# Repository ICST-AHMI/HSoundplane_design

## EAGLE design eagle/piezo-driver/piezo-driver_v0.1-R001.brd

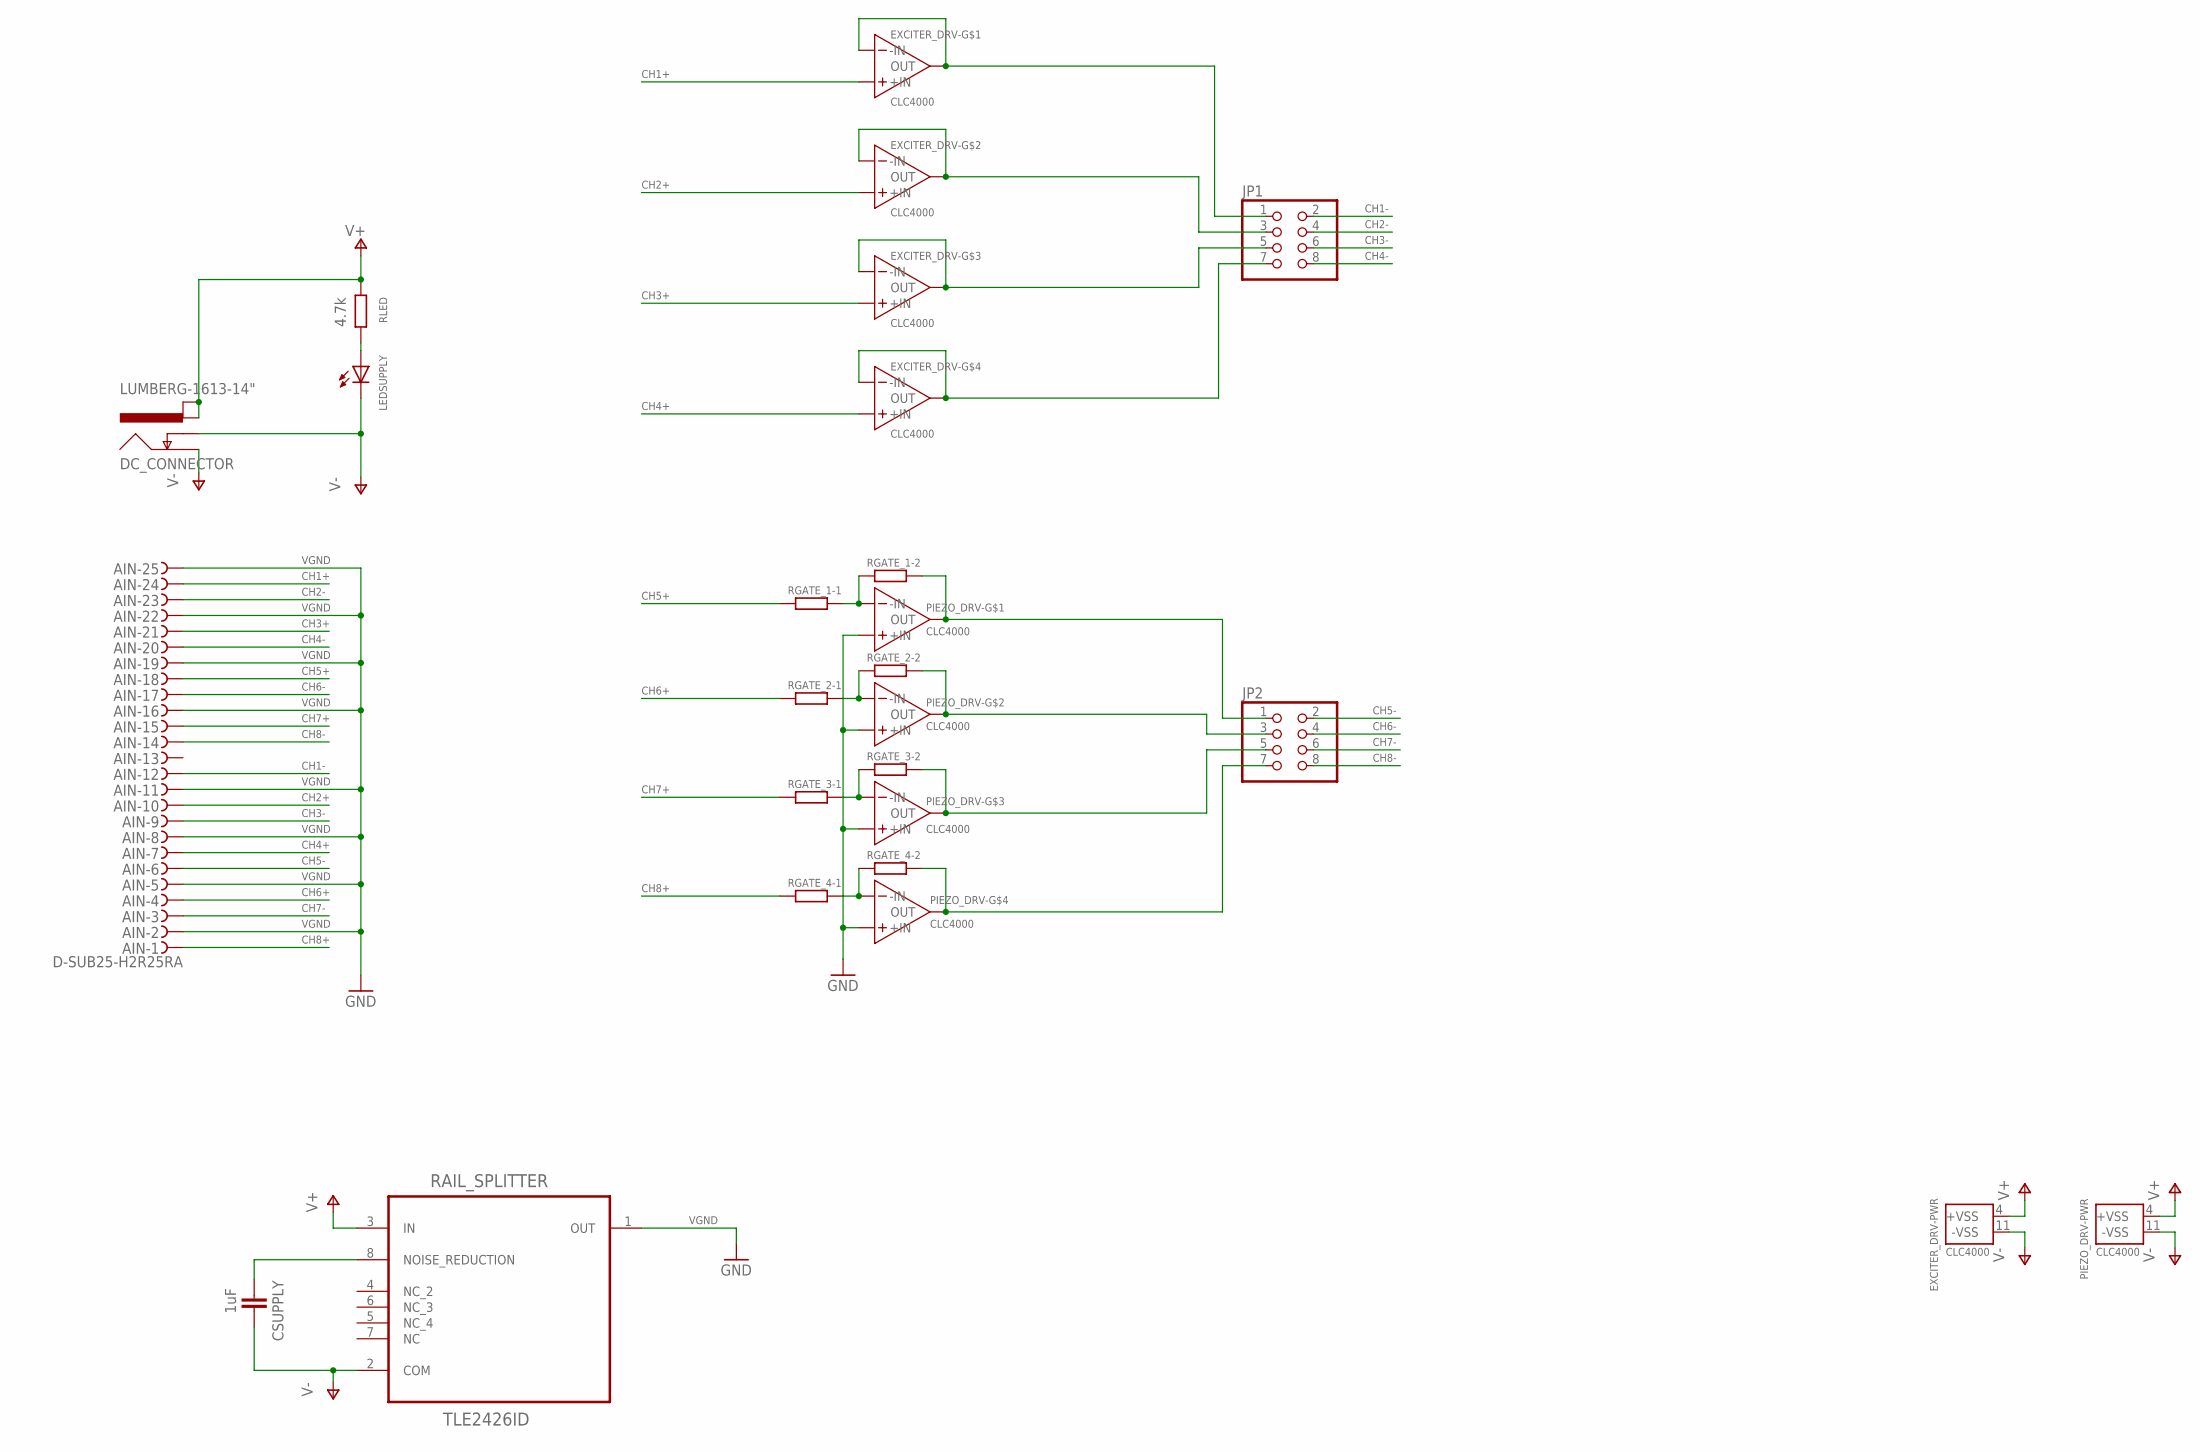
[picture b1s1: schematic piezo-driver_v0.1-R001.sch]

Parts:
AIN: D-SUB25-H2R25RA; H2R25RA
CSUPPLY: 1uF; C0603
DC_CONNECTOR: LUMBERG-1613-14"; LUMBERG-1613_14
EXCITER_DRV: CLC4000; SOIC-14
JP1, JP2: PINHD-2X4/90; 2X04/90
LEDSUPPLY: LED3MM
PIEZO_DRV: CLC4000; SOIC-14
RAIL_SPLITTER: TLE2426ID; SOIC127P600X175-8N
RGATE_1-1, RGATE_1-2, RGATE_2-1, RGATE_2-2, RGATE_3-1, RGATE_3-2, RGATE_4-1, RGATE_4-2: R-EU_R0805; R0805
RLED: 4.7k; R0805

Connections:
CH1+: AIN.24, EXCITER_DRV.3 (+IN)
CH1-: AIN.12, JP1.2
CH2+: AIN.10, EXCITER_DRV.5 (+IN)
CH2-: AIN.23, JP1.4
CH3+: AIN.21, EXCITER_DRV.10 (+IN)
CH3-: AIN.9, JP1.6
CH4+: AIN.7, EXCITER_DRV.12 (+IN)
CH4-: AIN.20, JP1.8
CH5+: AIN.18, RGATE_1-1.1
CH5-: AIN.6, JP2.2
CH6+: AIN.4, RGATE_2-1.1
CH6-: AIN.17, JP2.4
CH7+: AIN.15, RGATE_3-1.1
CH7-: AIN.3, JP2.6
CH8+: AIN.1, RGATE_4-1.1
CH8-: AIN.14, JP2.8
unnamed: EXCITER_DRV.1 (OUT), EXCITER_DRV.2 (-IN), JP1.1
unnamed: EXCITER_DRV.6 (-IN), EXCITER_DRV.7 (OUT), JP1.3
unnamed: EXCITER_DRV.8 (OUT), EXCITER_DRV.9 (-IN), JP1.5
unnamed: EXCITER_DRV.13 (-IN), EXCITER_DRV.14 (OUT), JP1.7
unnamed: CSUPPLY.1, RAIL_SPLITTER.8 (NOISE_REDUCTION)
unnamed: PIEZO_DRV.2 (-IN), RGATE_1-1.2, RGATE_1-2.1
unnamed: JP2.1, PIEZO_DRV.1 (OUT), RGATE_1-2.2
unnamed: PIEZO_DRV.6 (-IN), RGATE_2-1.2, RGATE_2-2.1
unnamed: JP2.3, PIEZO_DRV.7 (OUT), RGATE_2-2.2
unnamed: PIEZO_DRV.9 (-IN), RGATE_3-1.2, RGATE_3-2.1
unnamed: JP2.5, PIEZO_DRV.8 (OUT), RGATE_3-2.2
unnamed: PIEZO_DRV.13 (-IN), RGATE_4-1.2, RGATE_4-2.1
unnamed: JP2.7, PIEZO_DRV.14 (OUT), RGATE_4-2.2
unnamed: LEDSUPPLY.A, RLED.1
V+: DC_CONNECTOR.3 (PWR_1), DC_CONNECTOR.4 (PWR_2), EXCITER_DRV.4 (+VSS), PIEZO_DRV.4 (+VSS), RAIL_SPLITTER.3 (IN), RLED.2
V-: CSUPPLY.2, DC_CONNECTOR.1 (GND), DC_CONNECTOR.2 (GND_INS), EXCITER_DRV.11 (-VSS), LEDSUPPLY.K (C), PIEZO_DRV.11 (-VSS), RAIL_SPLITTER.2 (COM)
VGND: AIN.2, AIN.5, AIN.8, AIN.11, AIN.16, AIN.19, AIN.22, AIN.25, PIEZO_DRV.3 (+IN), PIEZO_DRV.5 (+IN), PIEZO_DRV.10 (+IN), PIEZO_DRV.12 (+IN), RAIL_SPLITTER.1 (OUT)

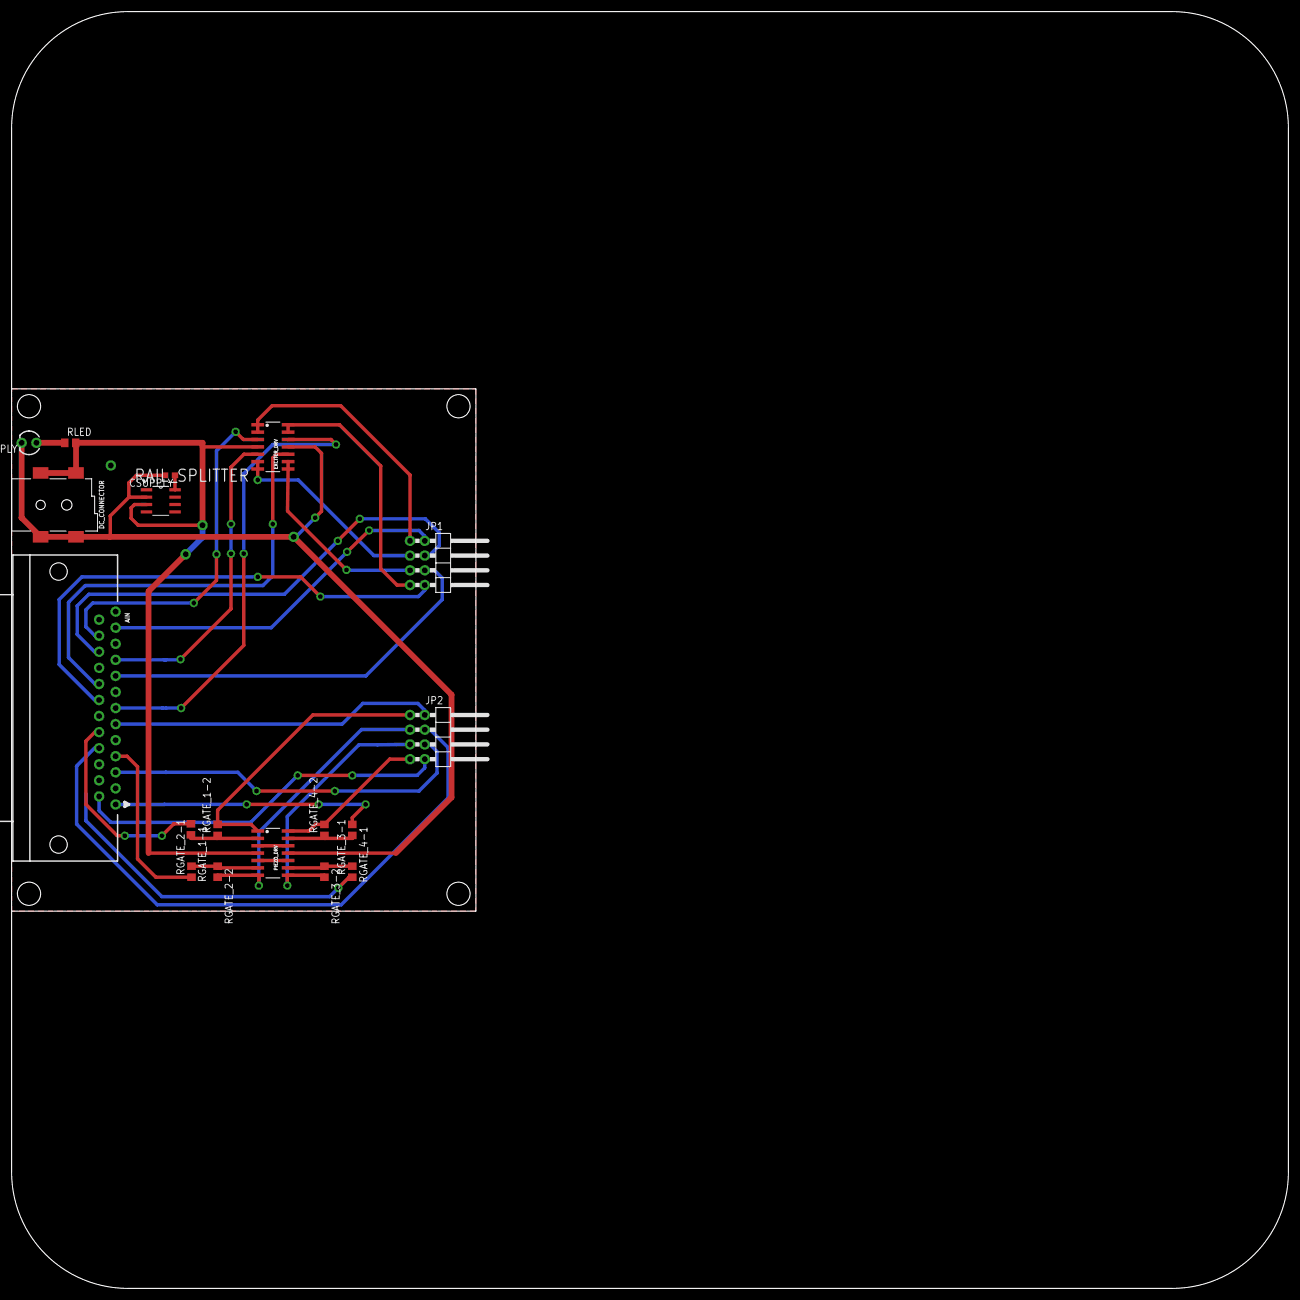
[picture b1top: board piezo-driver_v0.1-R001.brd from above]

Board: 2 copper layers, 220.0 x 220.0 mm, 18 parts (0 on the bottom side), 33 nets.

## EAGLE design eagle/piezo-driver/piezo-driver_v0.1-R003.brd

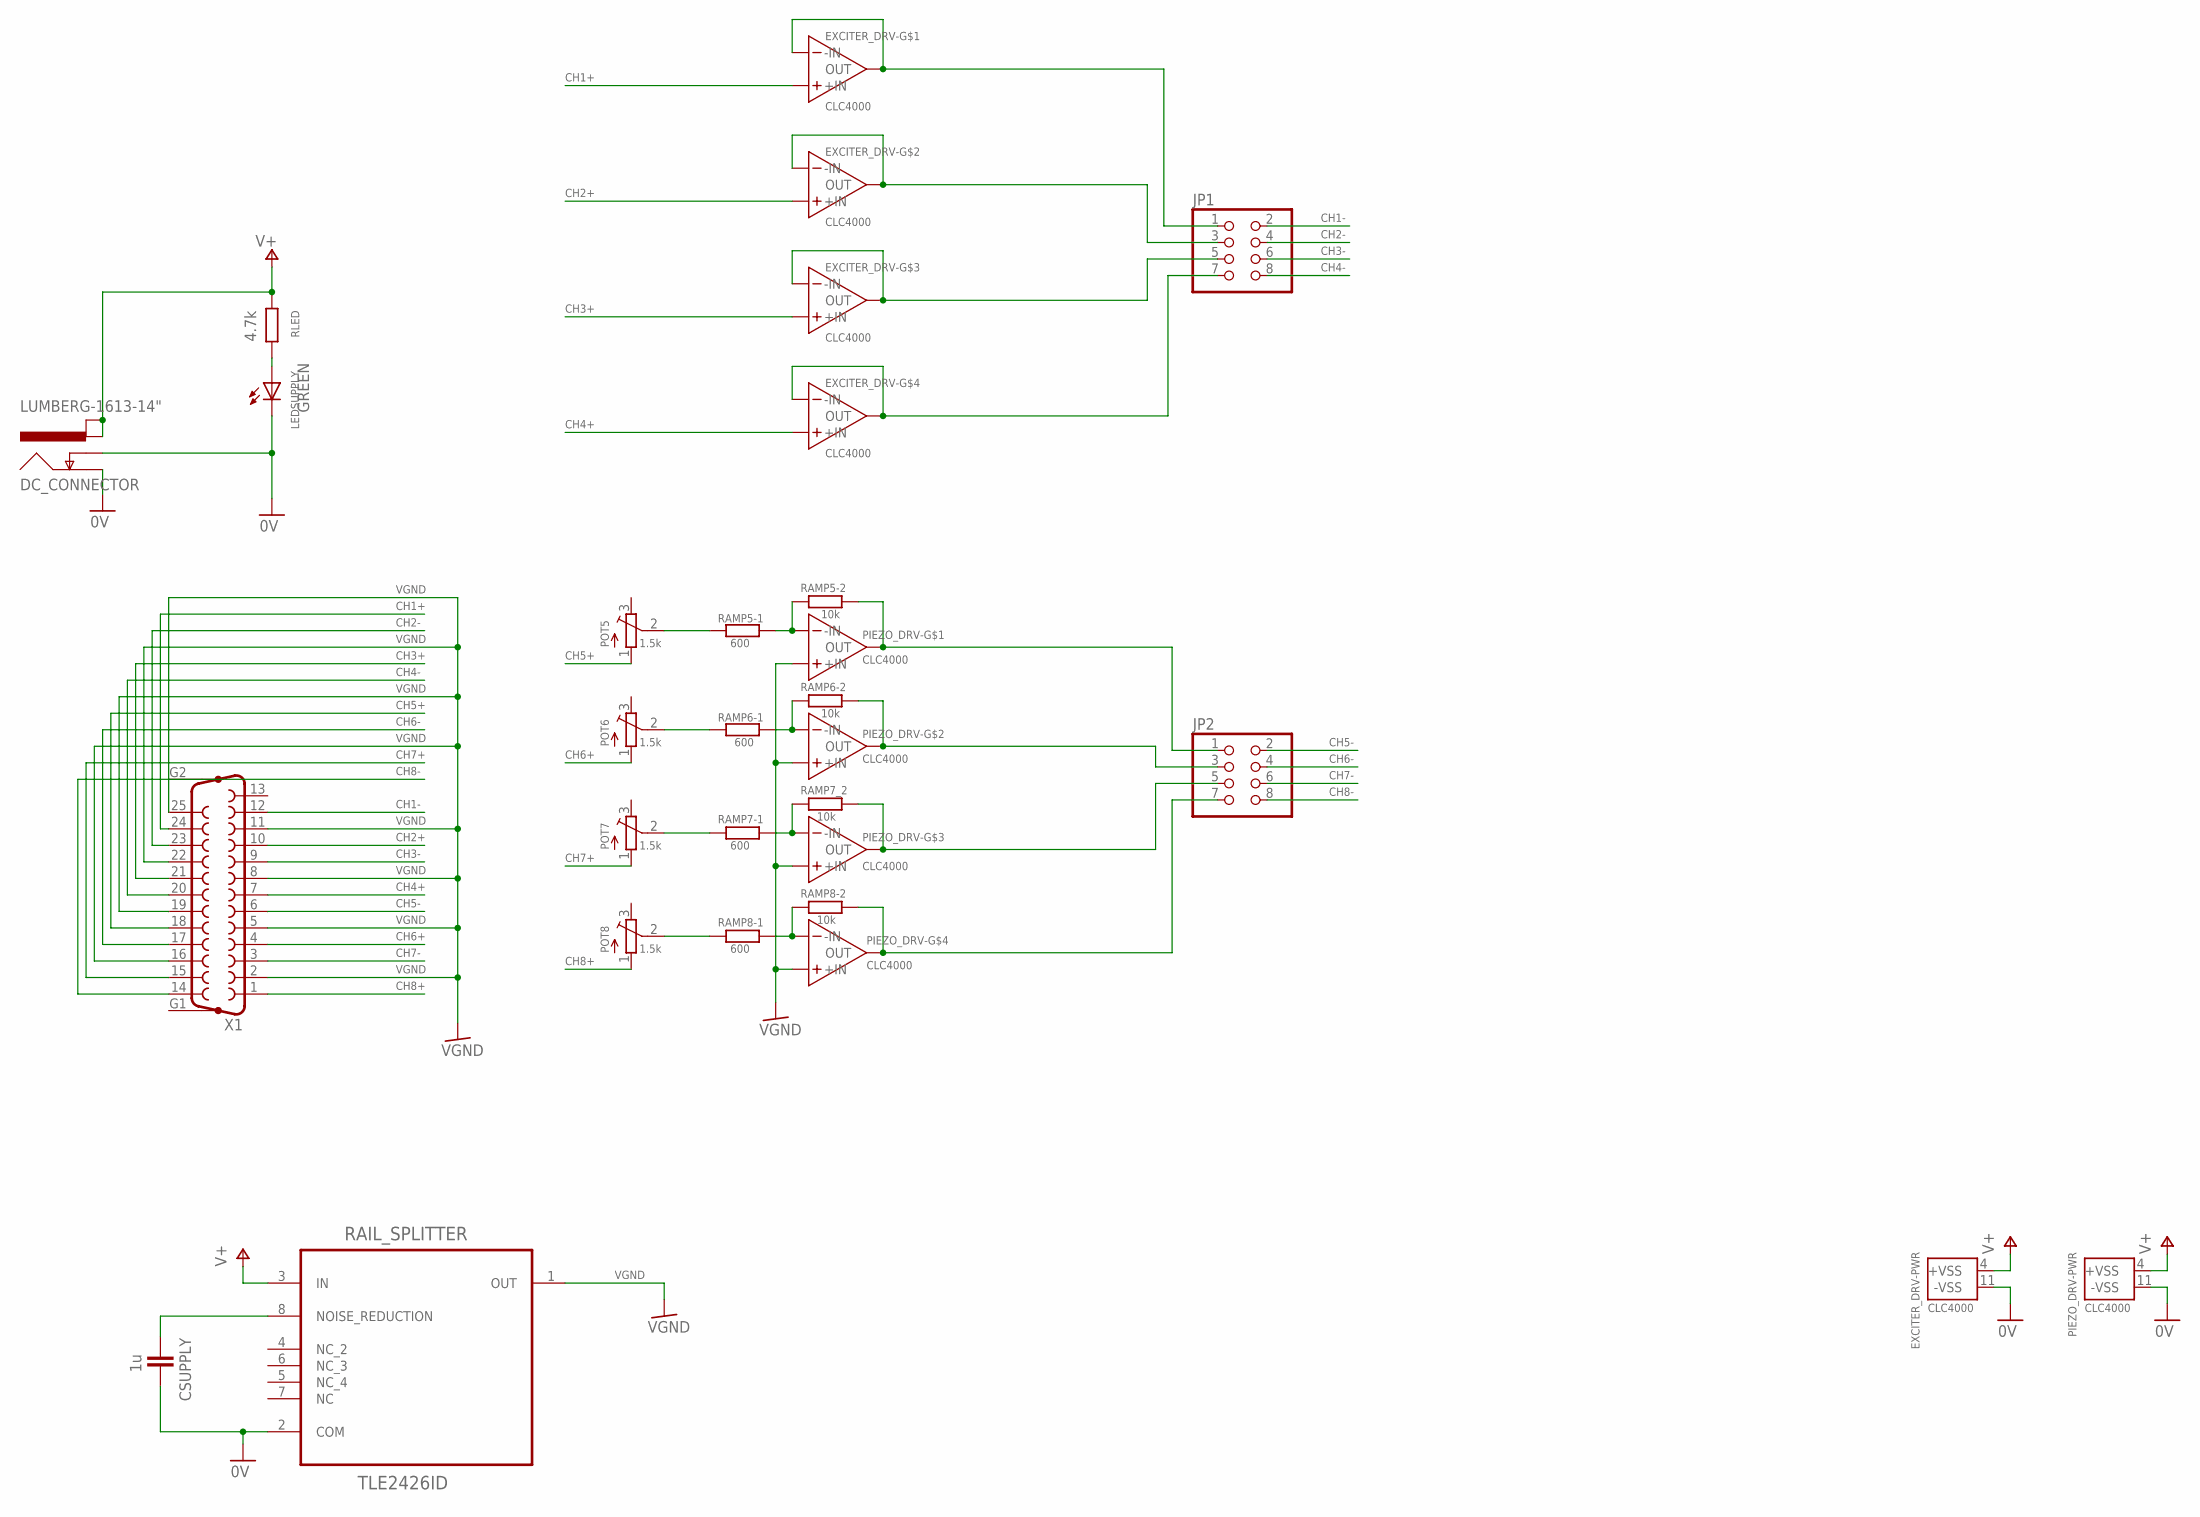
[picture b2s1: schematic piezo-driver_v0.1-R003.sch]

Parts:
CSUPPLY: 1u; C0603
DC_CONNECTOR: LUMBERG-1613-14"; LUMBERG-1613_14
EXCITER_DRV: CLC4000; SOIC-14
JP1, JP2: PINHD-2X4/90; 2X04/90
LEDSUPPLY: GREEN; LED3MM
PIEZO_DRV: CLC4000; SOIC-14
POT5, POT6, POT7, POT8: 1.5k; PVG3
RAIL_SPLITTER: TLE2426ID; SOIC127P600X175-8N
RAMP5-1, RAMP6-1, RAMP7-1, RAMP8-1: 600; R0805
RAMP5-2, RAMP6-2, RAMP7_2, RAMP8-2: 10k; R0805
RLED: 4.7k; R0805
X1: F25HP

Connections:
CH1+: EXCITER_DRV.3 (+IN), X1.24
CH1-: JP1.2, X1.12
CH2+: EXCITER_DRV.5 (+IN), X1.10
CH2-: JP1.4, X1.23
CH3+: EXCITER_DRV.10 (+IN), X1.21
CH3-: JP1.6, X1.9
CH4+: EXCITER_DRV.12 (+IN), X1.7
CH4-: JP1.8, X1.20
CH5+: POT5.1 (A), X1.18
CH5-: JP2.2, X1.6
CH6+: POT6.1 (A), X1.4
CH6-: JP2.4, X1.17
CH7+: POT7.1 (A), X1.15
CH7-: JP2.6, X1.3
CH8+: POT8.1 (A), X1.1
CH8-: JP2.8, X1.14
unnamed: EXCITER_DRV.1 (OUT), EXCITER_DRV.2 (-IN), JP1.1
unnamed: EXCITER_DRV.6 (-IN), EXCITER_DRV.7 (OUT), JP1.3
unnamed: EXCITER_DRV.8 (OUT), EXCITER_DRV.9 (-IN), JP1.5
unnamed: EXCITER_DRV.13 (-IN), EXCITER_DRV.14 (OUT), JP1.7
unnamed: CSUPPLY.1, RAIL_SPLITTER.8 (NOISE_REDUCTION)
unnamed: PIEZO_DRV.2 (-IN), RAMP5-1.2, RAMP5-2.1
unnamed: JP2.1, PIEZO_DRV.1 (OUT), RAMP5-2.2
unnamed: PIEZO_DRV.6 (-IN), RAMP6-1.2, RAMP6-2.1
unnamed: JP2.3, PIEZO_DRV.7 (OUT), RAMP6-2.2
unnamed: PIEZO_DRV.9 (-IN), RAMP7-1.2, RAMP7_2.1
unnamed: JP2.5, PIEZO_DRV.8 (OUT), RAMP7_2.2
unnamed: PIEZO_DRV.13 (-IN), RAMP8-1.2, RAMP8-2.1
unnamed: JP2.7, PIEZO_DRV.14 (OUT), RAMP8-2.2
unnamed: LEDSUPPLY.A, RLED.1
unnamed: POT5.2 (S), RAMP5-1.1
unnamed: POT6.2 (S), RAMP6-1.1
unnamed: POT7.2 (S), RAMP7-1.1
unnamed: POT8.2 (S), RAMP8-1.1
V+: DC_CONNECTOR.3 (PWR_1), DC_CONNECTOR.4 (PWR_2), EXCITER_DRV.4 (+VSS), PIEZO_DRV.4 (+VSS), RAIL_SPLITTER.3 (IN), RLED.2
V-: CSUPPLY.2, DC_CONNECTOR.1 (GND), DC_CONNECTOR.2 (GND_INS), EXCITER_DRV.11 (-VSS), LEDSUPPLY.K (C), PIEZO_DRV.11 (-VSS), RAIL_SPLITTER.2 (COM)
VGND: PIEZO_DRV.3 (+IN), PIEZO_DRV.5 (+IN), PIEZO_DRV.10 (+IN), PIEZO_DRV.12 (+IN), RAIL_SPLITTER.1 (OUT), X1.2, X1.5, X1.8, X1.11, X1.16, X1.19, X1.22, X1.25

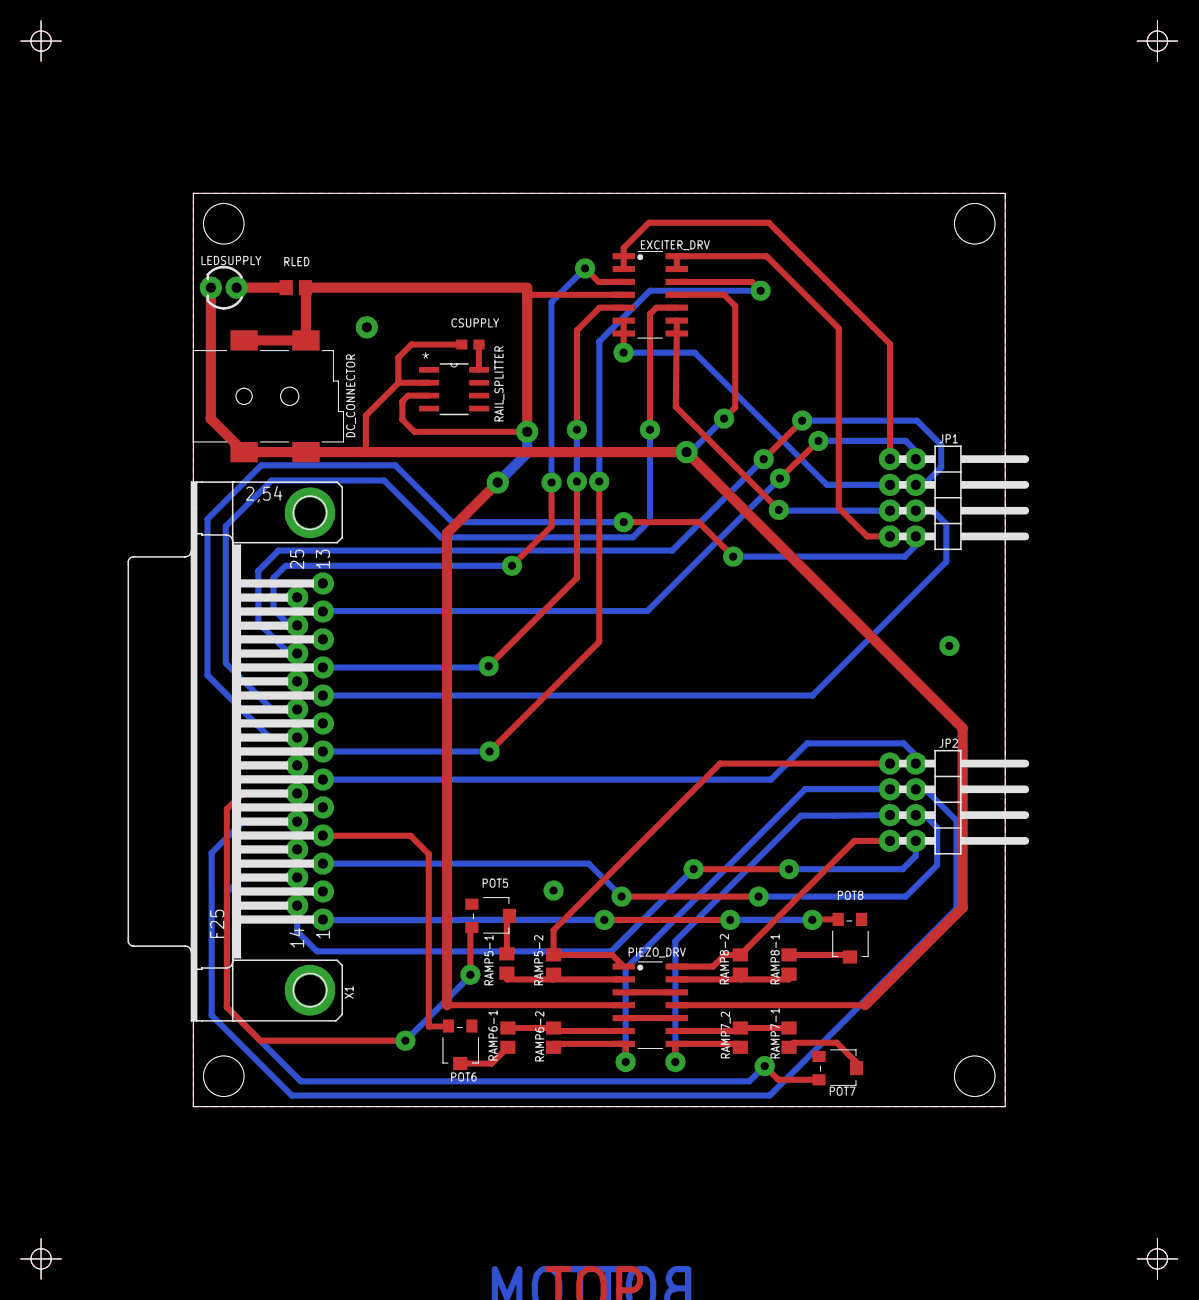
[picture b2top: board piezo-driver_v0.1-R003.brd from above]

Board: 2 copper layers, 80.0 x 90.0 mm, 22 parts (0 on the bottom side), 37 nets.

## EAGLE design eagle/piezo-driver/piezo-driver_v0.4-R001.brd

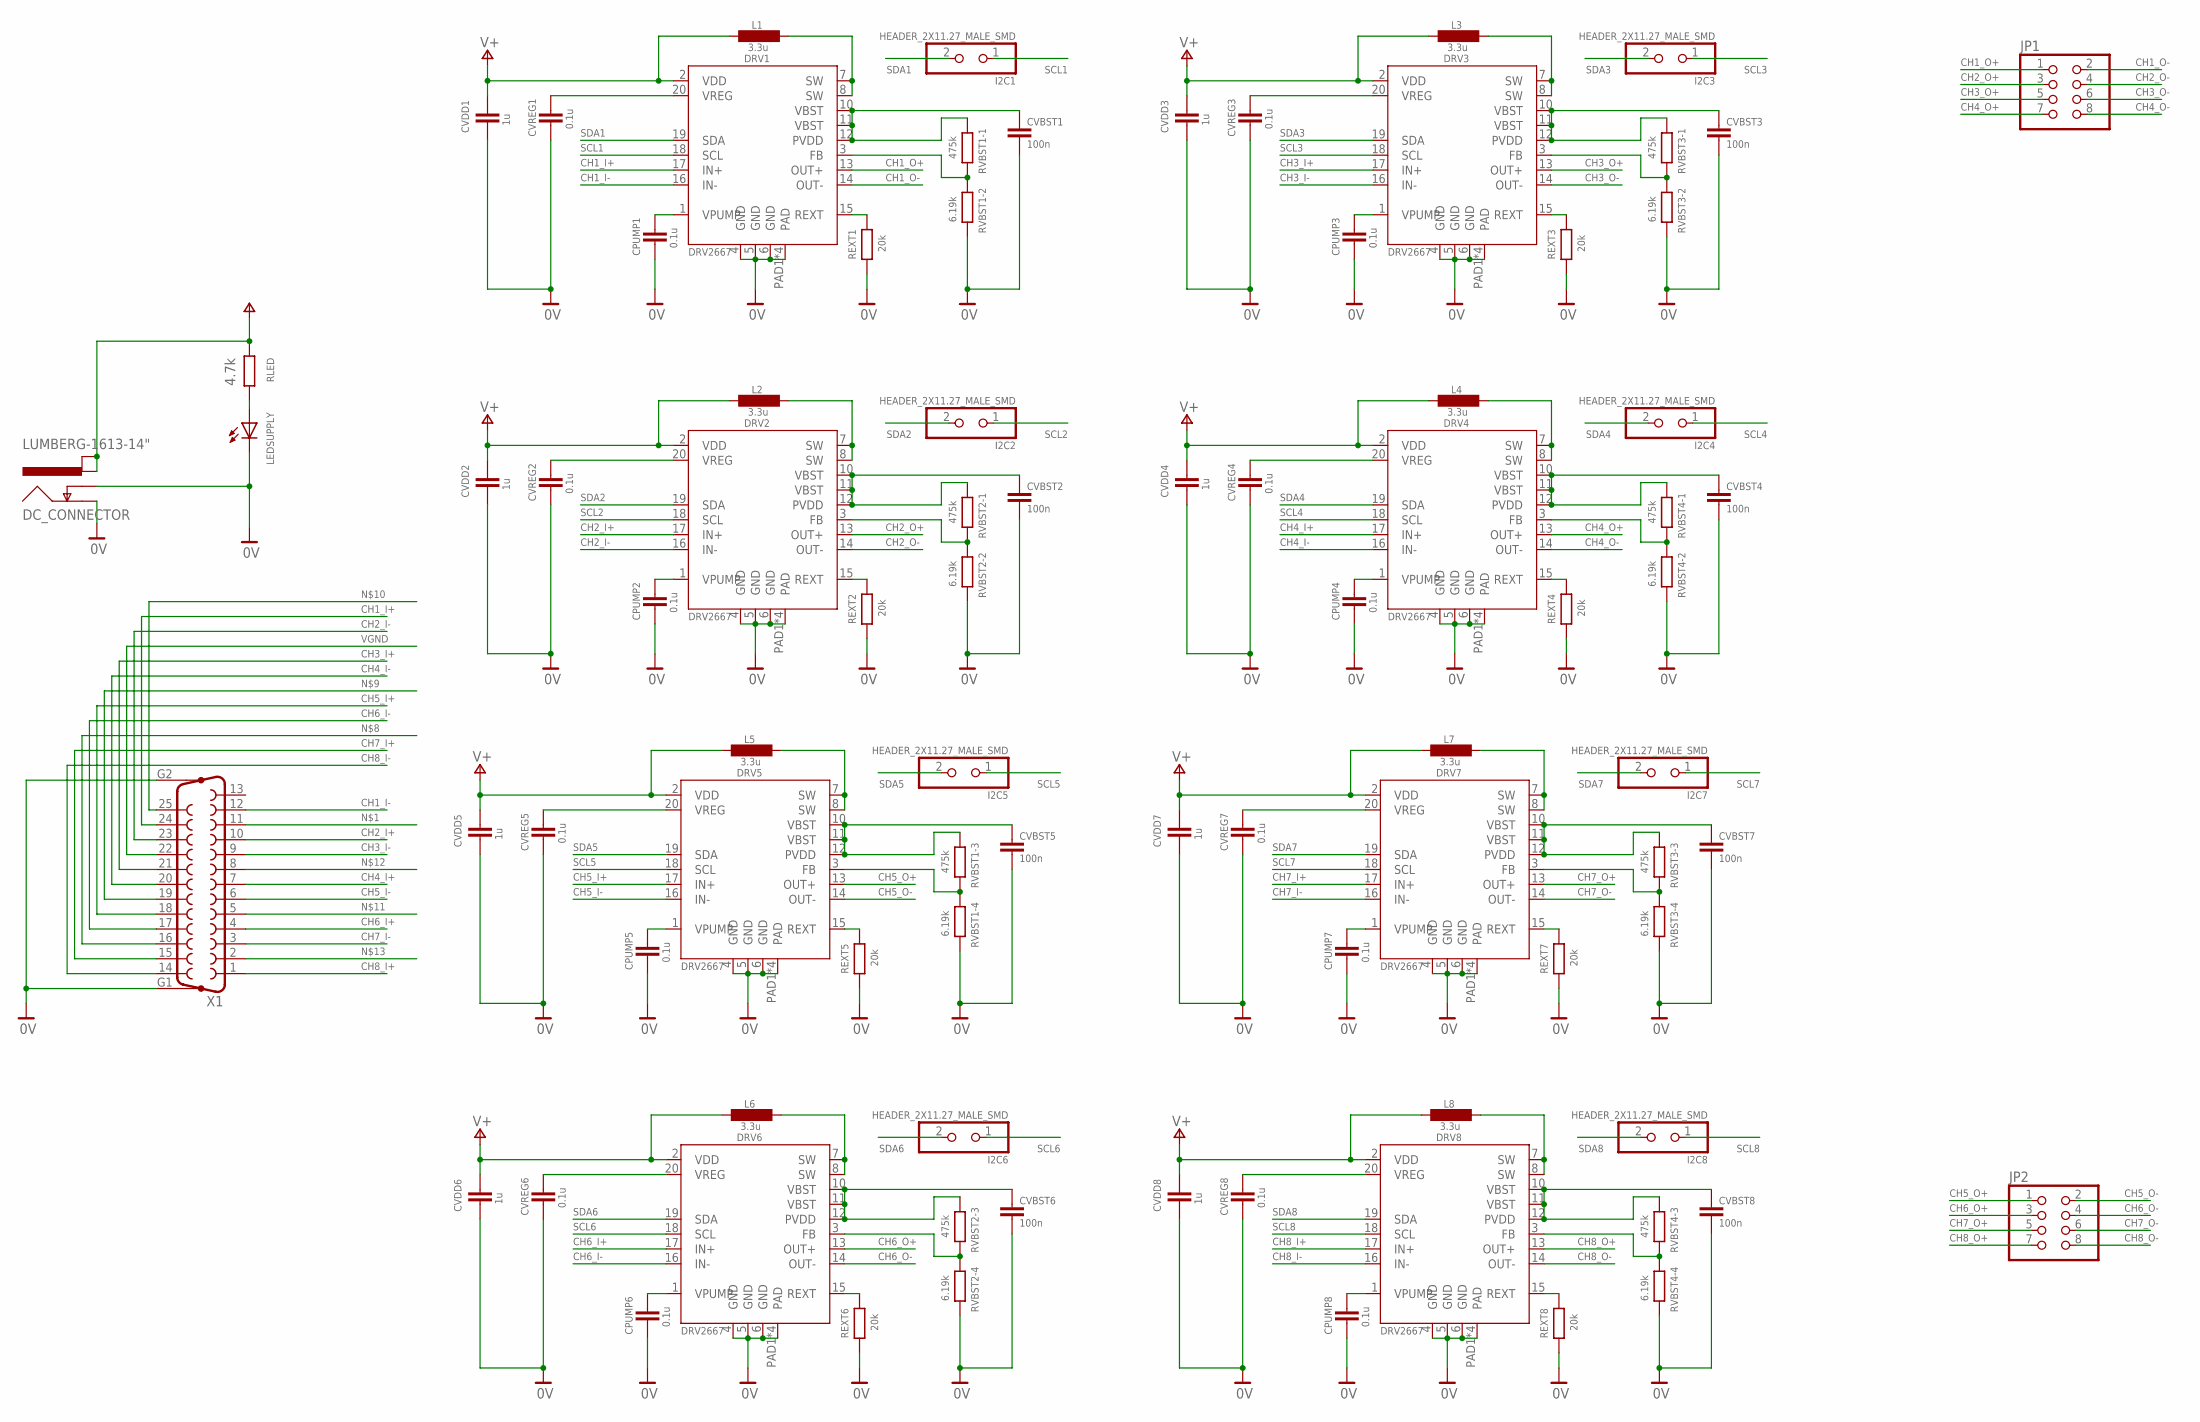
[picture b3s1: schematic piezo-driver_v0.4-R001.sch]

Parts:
CPUMP1, CPUMP2, CPUMP3, CPUMP4, CPUMP5, CPUMP6, CPUMP7, CPUMP8: 0.1u; C0805
CVBST1, CVBST2, CVBST3, CVBST4, CVBST5, CVBST6, CVBST7, CVBST8: 100n; C0805
CVDD1, CVDD2, CVDD3, CVDD4, CVDD5, CVDD6, CVDD7, CVDD8: 1u; C0805
CVREG1, CVREG2, CVREG3, CVREG4, CVREG5, CVREG6, CVREG7, CVREG8: 0.1u; C0805
DC_CONNECTOR: LUMBERG-1613-14"; LUMBERG-1613_14
DRV1, DRV2, DRV3, DRV4, DRV5, DRV6, DRV7, DRV8: DRV2667QFN; QFN400X400
I2C1, I2C2, I2C3, I2C4, I2C5, I2C6, I2C7, I2C8: HEADER_2X11.27_MALE_SMD; 2X01_1.27_SMD
JP1, JP2: PINHD-2X4/90; 2X04/90
L1, L2, L3, L4, L5, L6, L7, L8: 3.3u; L3225M
LEDSUPPLY: LED0603; LED-0603
REXT1, REXT2, REXT3, REXT4, REXT5, REXT6, REXT7, REXT8: 20k; R0805
RLED: 4.7k; R0805
RVBST1-1, RVBST1-3, RVBST2-1, RVBST2-3, RVBST3-1, RVBST3-3, RVBST4-1, RVBST4-3: 475k; R0805
RVBST1-2, RVBST1-4, RVBST2-2, RVBST2-4, RVBST3-2, RVBST3-4, RVBST4-2, RVBST4-4: 6.19k; R0805
X1: F25HP

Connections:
0V: CPUMP1.2, CPUMP2.2, CPUMP3.2, CPUMP4.2, CPUMP5.2, CPUMP6.2, CPUMP7.2, CPUMP8.2, CVBST1.2, CVBST2.2, CVBST3.2, CVBST4.2, CVBST5.2, CVBST6.2, CVBST7.2, CVBST8.2, CVDD1.2, CVDD2.2, CVDD3.2, CVDD4.2, CVDD5.2, CVDD6.2, CVDD7.2, CVDD8.2, CVREG1.2, CVREG2.2, CVREG3.2, CVREG4.2, CVREG5.2, CVREG6.2, CVREG7.2, CVREG8.2, DC_CONNECTOR.1 (GND), DC_CONNECTOR.2 (GND_INS), DRV1.4 (GND), DRV1.5 (GND), DRV1.6 (GND), DRV1.PAD1 (PAD), DRV1.PAD2 (PAD), DRV1.PAD3 (PAD), DRV1.PAD4 (PAD), DRV2.4 (GND), DRV2.5 (GND), DRV2.6 (GND), DRV2.PAD1 (PAD), DRV2.PAD2 (PAD), DRV2.PAD3 (PAD), DRV2.PAD4 (PAD), DRV3.4 (GND), DRV3.5 (GND), DRV3.6 (GND), DRV3.PAD1 (PAD), DRV3.PAD2 (PAD), DRV3.PAD3 (PAD), DRV3.PAD4 (PAD), DRV4.4 (GND), DRV4.5 (GND), DRV4.6 (GND), DRV4.PAD1 (PAD), DRV4.PAD2 (PAD), DRV4.PAD3 (PAD), DRV4.PAD4 (PAD), DRV5.4 (GND), DRV5.5 (GND), DRV5.6 (GND), DRV5.PAD1 (PAD), DRV5.PAD2 (PAD), DRV5.PAD3 (PAD), DRV5.PAD4 (PAD), DRV6.4 (GND), DRV6.5 (GND), DRV6.6 (GND), DRV6.PAD1 (PAD), DRV6.PAD2 (PAD), DRV6.PAD3 (PAD), DRV6.PAD4 (PAD), DRV7.4 (GND), DRV7.5 (GND), DRV7.6 (GND), DRV7.PAD1 (PAD), DRV7.PAD2 (PAD), DRV7.PAD3 (PAD), DRV7.PAD4 (PAD), DRV8.4 (GND), DRV8.5 (GND), DRV8.6 (GND), DRV8.PAD1 (PAD), DRV8.PAD2 (PAD), DRV8.PAD3 (PAD), DRV8.PAD4 (PAD), LEDSUPPLY.C, REXT1.1, REXT2.1, REXT3.1, REXT4.1, REXT5.1, REXT6.1, REXT7.1, REXT8.1, RVBST1-2.1, RVBST1-4.1, RVBST2-2.1, RVBST2-4.1, RVBST3-2.1, RVBST3-4.1, RVBST4-2.1, RVBST4-4.1, X1.G1, X1.G2
CH1_I+: DRV1.17 (IN+), X1.24
CH1_I-: DRV1.16 (IN-), X1.12
CH1_O+: DRV1.13 (OUT+), JP1.1
CH1_O-: DRV1.14 (OUT-), JP1.2
CH2_I+: DRV2.17 (IN+), X1.10
CH2_I-: DRV2.16 (IN-), X1.23
CH2_O+: DRV2.13 (OUT+), JP1.3
CH2_O-: DRV2.14 (OUT-), JP1.4
CH3_I+: DRV3.17 (IN+), X1.21
CH3_I-: DRV3.16 (IN-), X1.9
CH3_O+: DRV3.13 (OUT+), JP1.5
CH3_O-: DRV3.14 (OUT-), JP1.6
CH4_I+: DRV4.17 (IN+), X1.7
CH4_I-: DRV4.16 (IN-), X1.20
CH4_O+: DRV4.13 (OUT+), JP1.7
CH4_O-: DRV4.14 (OUT-), JP1.8
CH5_I+: DRV5.17 (IN+), X1.18
CH5_I-: DRV5.16 (IN-), X1.6
CH5_O+: DRV5.13 (OUT+), JP2.1
CH5_O-: DRV5.14 (OUT-), JP2.2
CH6_I+: DRV6.17 (IN+), X1.4
CH6_I-: DRV6.16 (IN-), X1.17
CH6_O+: DRV6.13 (OUT+), JP2.3
CH6_O-: DRV6.14 (OUT-), JP2.4
CH7_I+: DRV7.17 (IN+), X1.15
CH7_I-: DRV7.16 (IN-), X1.3
CH7_O+: DRV7.13 (OUT+), JP2.5
CH7_O-: DRV7.14 (OUT-), JP2.6
CH8_I+: DRV8.17 (IN+), X1.1
CH8_I-: DRV8.16 (IN-), X1.14
CH8_O+: DRV8.13 (OUT+), JP2.7
CH8_O-: DRV8.14 (OUT-), JP2.8
unnamed: DRV1.7 (SW), DRV1.8 (SW), L1.1
unnamed: CVBST1.1, DRV1.10 (VBST), DRV1.11 (VBST), DRV1.12 (PVDD), RVBST1-1.2
unnamed: DRV1.3 (FB), RVBST1-1.1, RVBST1-2.2
unnamed: DRV1.15 (REXT), REXT1.2
unnamed: CPUMP1.1, DRV1.1 (VPUMP)
unnamed: CVREG1.1, DRV1.20 (VREG)
unnamed: DRV2.7 (SW), DRV2.8 (SW), L2.1
unnamed: LEDSUPPLY.A, RLED.1
unnamed: CVBST2.1, DRV2.10 (VBST), DRV2.11 (VBST), DRV2.12 (PVDD), RVBST2-1.2
unnamed: DRV2.3 (FB), RVBST2-1.1, RVBST2-2.2
unnamed: DRV2.15 (REXT), REXT2.2
unnamed: CPUMP2.1, DRV2.1 (VPUMP)
unnamed: CVREG2.1, DRV2.20 (VREG)
unnamed: DRV3.7 (SW), DRV3.8 (SW), L3.1
unnamed: CVBST3.1, DRV3.10 (VBST), DRV3.11 (VBST), DRV3.12 (PVDD), RVBST3-1.2
unnamed: DRV3.3 (FB), RVBST3-1.1, RVBST3-2.2
unnamed: DRV3.15 (REXT), REXT3.2
unnamed: CPUMP3.1, DRV3.1 (VPUMP)
unnamed: CVREG3.1, DRV3.20 (VREG)
unnamed: DRV4.7 (SW), DRV4.8 (SW), L4.1
unnamed: CVBST4.1, DRV4.10 (VBST), DRV4.11 (VBST), DRV4.12 (PVDD), RVBST4-1.2
unnamed: DRV4.3 (FB), RVBST4-1.1, RVBST4-2.2
unnamed: DRV4.15 (REXT), REXT4.2
unnamed: CPUMP4.1, DRV4.1 (VPUMP)
unnamed: CVREG4.1, DRV4.20 (VREG)
unnamed: DRV5.7 (SW), DRV5.8 (SW), L5.1
unnamed: CVBST5.1, DRV5.10 (VBST), DRV5.11 (VBST), DRV5.12 (PVDD), RVBST1-3.2
unnamed: DRV5.3 (FB), RVBST1-3.1, RVBST1-4.2
unnamed: DRV5.15 (REXT), REXT5.2
unnamed: CPUMP5.1, DRV5.1 (VPUMP)
unnamed: CVREG5.1, DRV5.20 (VREG)
unnamed: DRV6.7 (SW), DRV6.8 (SW), L6.1
unnamed: CVBST6.1, DRV6.10 (VBST), DRV6.11 (VBST), DRV6.12 (PVDD), RVBST2-3.2
unnamed: DRV6.3 (FB), RVBST2-3.1, RVBST2-4.2
unnamed: DRV6.15 (REXT), REXT6.2
unnamed: CPUMP6.1, DRV6.1 (VPUMP)
unnamed: CVREG6.1, DRV6.20 (VREG)
unnamed: DRV7.7 (SW), DRV7.8 (SW), L7.1
unnamed: CVBST7.1, DRV7.10 (VBST), DRV7.11 (VBST), DRV7.12 (PVDD), RVBST3-3.2
unnamed: DRV7.3 (FB), RVBST3-3.1, RVBST3-4.2
unnamed: DRV7.15 (REXT), REXT7.2
unnamed: CPUMP7.1, DRV7.1 (VPUMP)
unnamed: CVREG7.1, DRV7.20 (VREG)
unnamed: DRV8.7 (SW), DRV8.8 (SW), L8.1
unnamed: CVBST8.1, DRV8.10 (VBST), DRV8.11 (VBST), DRV8.12 (PVDD), RVBST4-3.2
unnamed: DRV8.3 (FB), RVBST4-3.1, RVBST4-4.2
unnamed: DRV8.15 (REXT), REXT8.2
unnamed: CPUMP8.1, DRV8.1 (VPUMP)
unnamed: CVREG8.1, DRV8.20 (VREG)
SCL1: DRV1.18 (SCL), I2C1.1
SCL2: DRV2.18 (SCL), I2C2.1
SCL3: DRV3.18 (SCL), I2C3.1
SCL4: DRV4.18 (SCL), I2C4.1
SCL5: DRV5.18 (SCL), I2C5.1
SCL6: DRV6.18 (SCL), I2C6.1
SCL7: DRV7.18 (SCL), I2C7.1
SCL8: DRV8.18 (SCL), I2C8.1
SDA1: DRV1.19 (SDA), I2C1.2
SDA2: DRV2.19 (SDA), I2C2.2
SDA3: DRV3.19 (SDA), I2C3.2
SDA4: DRV4.19 (SDA), I2C4.2
SDA5: DRV5.19 (SDA), I2C5.2
SDA6: DRV6.19 (SDA), I2C6.2
SDA7: DRV7.19 (SDA), I2C7.2
SDA8: DRV8.19 (SDA), I2C8.2
V+: CVDD1.1, CVDD2.1, CVDD3.1, CVDD4.1, CVDD5.1, CVDD6.1, CVDD7.1, CVDD8.1, DC_CONNECTOR.3 (PWR_1), DC_CONNECTOR.4 (PWR_2), DRV1.2 (VDD), DRV2.2 (VDD), DRV3.2 (VDD), DRV4.2 (VDD), DRV5.2 (VDD), DRV6.2 (VDD), DRV7.2 (VDD), DRV8.2 (VDD), L1.2, L2.2, L3.2, L4.2, L5.2, L6.2, L7.2, L8.2, RLED.2
VGND: X1.22

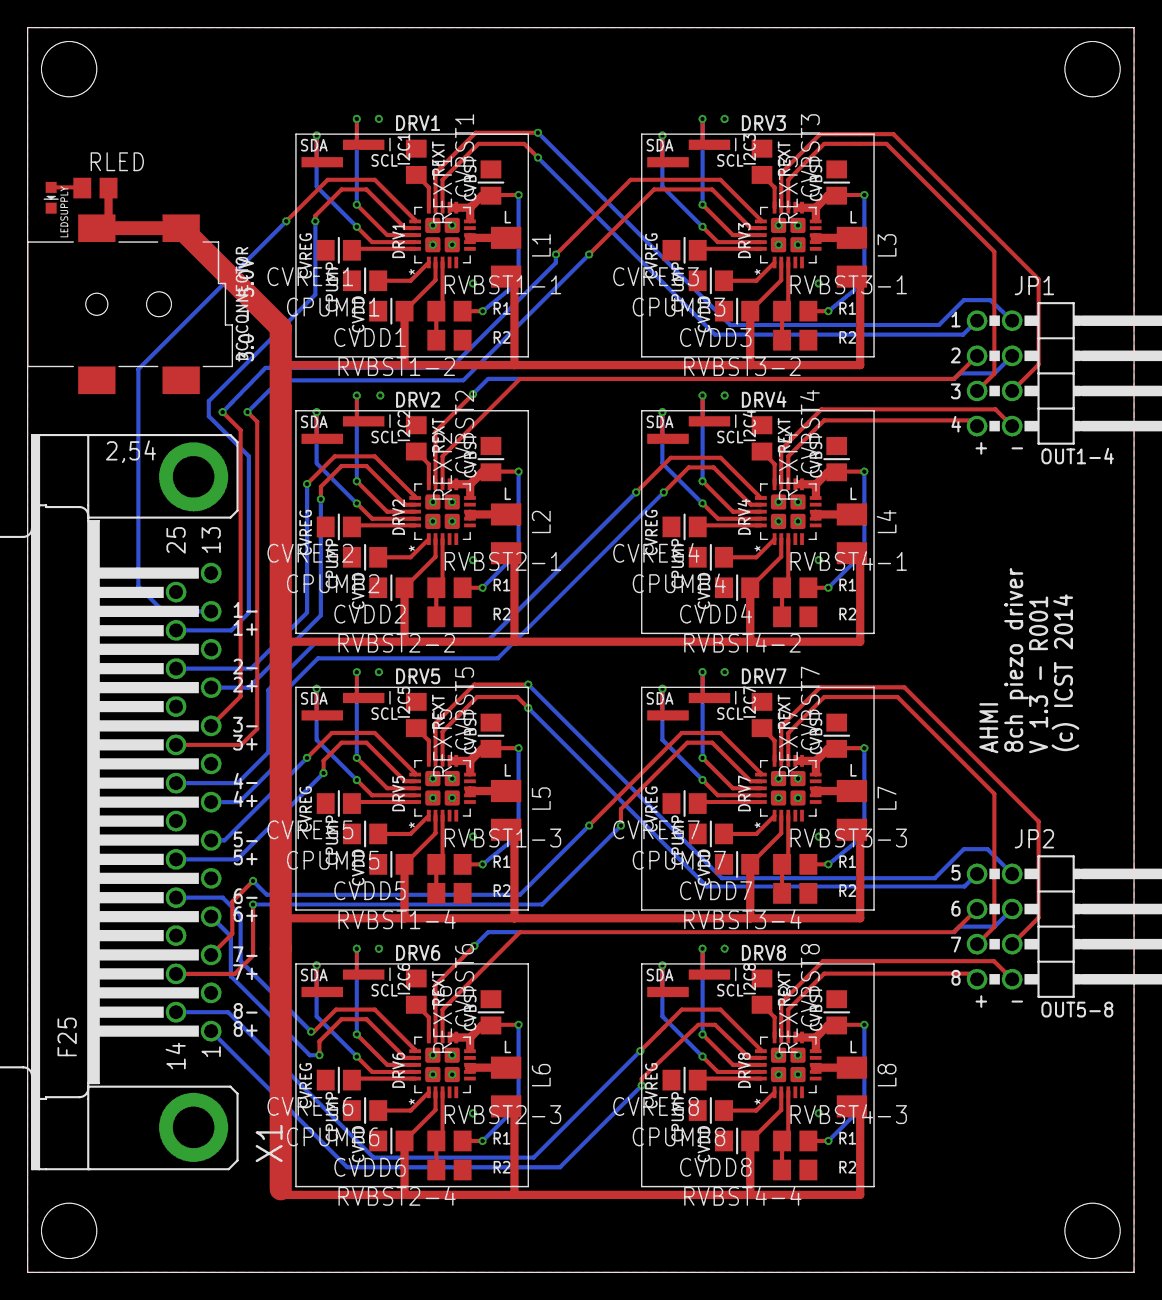
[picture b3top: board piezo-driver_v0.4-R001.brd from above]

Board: 2 copper layers, 80.0 x 90.0 mm, 86 parts (0 on the bottom side), 99 nets.
